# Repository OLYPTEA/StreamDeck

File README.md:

# KORE DECK

<h3 align="center">
Un Hub de Control Modulaire pour PC et Robotique/A Modular Stream Deck & Robotics Control Hub (cf : Robotic_Arm)
</h3>

---

##  Video de présentation/Cinematic Demo

https://github.com/user-attachments/assets/3f7520e6-ee07-4d92-a84f-97e8f2b0d568

---

## Description

Ce projet est un **Stream Deck DIY** développé dans le but d'être modulaire.  
Conçu autour d'un **ESP32-S3**, il permet de piloter des raccourcis PC, de monitorer des ressources, mais aussi de servir de **Hub de contrôle** pour des périphériques externes (bras robotique, capteurs) via un port d'extension dédié.

This project is a **DIY Stream Deck** designed to be modular.  
Built around an **ESP32-S3**, it allows you to control PC shortcuts, monitor system resources, and serve as a **control hub** for external devices (such as robotic arms and sensors) via a dedicated expansion port.

---

# Spécifications Matérielles

| Composant | Détails |
| :--- | :--- |
| **Microcontrôleur** | ESP32-S3 DevKit N16R8 (16MB Flash / 8MB PSRAM) |
| **Écran** | DWIN HMI 960x240 (Interface UART, protocole DGUS II) |
| **Capteurs** | 7x Switchs mécaniques (Cherry MX) + 4x Potentiomètres analogiques |
| **Alimentation** | USB-C natif (Compatible **Thunderbolt** pour forte puissance) |
| **Modularité** | Boîtier CAO avec pied indépendant et port d'extension I2C |

---

# Points Forts du Projet

## 1. Conception Modulaire (CAO)

Le boîtier a été conçu sous **Fusion 360** avec une approche modulaire :

- **Pied indépendant :**  
  Permet d'adapter différents angles ou supports (pince de bureau, bras articulé).

- **Port d'extension :**  
  Sortie des ports non-utilisés (SDA/SCL, 5V, GND) sur le côté pour connecter des modules sans ouvrir le boîtier.

- **Modularité du Software/Firmware**
  Pensé dans le but d'être mobile et évolutif (rajout facile à intégrer)

The Case was designed in **Fusion 360** using a modular approach:

- **Detachable stand:**  
  Allows for different angles or mounts (desk clamp, articulated arm).

- **Expansion port:**  
  Unused ports (SDA/SCL, 5V, GND) are routed to the side to connect modules without opening the enclosure.

- **Software/Firmware Modularity**
  Designed to be portable and scalable (easy to integrate new features)

---

## 2. Hub Robotique/Robotics Hub

Grâce au port d'extension, le Stream Deck peut piloter un **bras robotique** (servomoteurs) via un driver **PCA9685**.

- **Mapping dynamique :**  
  Les potentiomètres contrôlent directement les angles des servos lorsque le profil `Robot` est sélectionné.

- **Affichage temps réel :**  
  L'écran DWIN affiche l'état et la position de chaque articulation.

Thanks to the expansion port, the Stream Deck can control a **robotic arm** (servo motors) via a **PCA9685** driver.

- **Dynamic mapping:**  
  The potentiometers directly control the servo angles when the `Robot` profile is selected.

- **Real-time display:**  
  The DWIN screen displays the status and position of each joint.

---

## 3. Gestion de l'Énergie/Energy Management

Optimisation pour le **Thunderbolt** :

- Alimentation directe des périphériques (Écran, Servos) via la ligne **5V/Vin** pour préserver le régulateur interne de l'ESP32.

- Filtrage matériel par condensateurs (`470µF` → `1000µF`) pour stabiliser les pics de courant des moteurs.

Optimization for **Thunderbolt**:

- Direct power supply to peripherals (display, servos) via the **5V/Vin** line to preserve the ESP32’s internal voltage regulator.

- Hardware filtering using capacitors (`470µF` → `1000µF`) to stabilize motor current spikes.

---

# Schéma de Câblage (Résumé)/Wiring Diagram (Summary)

Le projet utilise des techniques de filtrage pour garantir la précision des lectures analogiques :

- **Potentiomètres :**  
  Condensateurs de `100nF` pour le lissage du signal.

- **Boutons :**  
  Condensateurs de `10nF` pour le debounce matériel.

- **Communication Écran :**  
  Liaison série directe (`3.3V TTL`) sur `Rx2/Tx2`.

The project uses filtering techniques to ensure the accuracy of analog readings:

- **Potentiometers:**  
  `100nF` capacitors for signal smoothing.

- **Buttons:**  
  `10nF` capacitors for hardware debouncing.

- **Display communication:**  
  Direct serial connection (`3.3V TTL`) on `Rx2/Tx2`.

---

# Structure du Dépôt/Structure of the Repository

```text
├── Hardware/           # Fichiers STEP/STL (Fusion 360)/STEP/STL files (Fusion 360)
├── Firmware/           # Code source ESP32 (Arduino IDE / PlatformIO)/ESP32 source code (Arduino IDE / PlatformIO)
├── DWIN_Project/       # Fichiers de configuration DGUS II (Interface graphique)/DGUS II Configuration Files (Graphical Interface)
├── Scripts_PC/         # Script de détection d'application (Python/C#)/Application detection script (Python/C#)
└── Assets/             # Icônes, vidéos et ressources graphiques/Icons, videos, and graphic resources
```

---

# Roadmap

- [ ] Interface UI avancée/Advanced UI (check)
- [ ] Gestion multi-profils/Multi-profile management (check)
- [ ] Intégration MQTT/MQTT integration
- [ ] Contrôle robotique avancé/Advanced robotics control
- [ ] Support Wi-Fi / Bluetooth/Wi-Fi / Bluetooth support
- [ ] Intégration Home Assistant/Home Assistant integration

---

# Technologies Utilisées/Technologies Used

- **ESP32-S3**
- **DGUS II / DWIN HMI**
- **Fusion 360**
- **Arduino / PlatformIO**
- **Python / C++**
- **I2C / UART**
- **KicKad**

---

# Auteur/Author

Projet conçu et développé par **OLYPTEA** (Sacha Gibert).

Project designed and developed by **OLYPTEA** (Sacha Gibert).

GitHub :  
https://github.com/OLYPTEA

---

Mention à Andrei Doncescu : https://homepages.laas.fr/adoncesc/SystemEmbed/Filtrage.pdf, 
          Random Nerds Tutorial : https://randomnerdtutorials.com/esp32-save-data-permanently-preferences/, 
          cppreference.com : https://en.cppreference.com/cpp/language/static_cast,
          Peng Zhihui : https://github.com/peng-zhihui/HoloCubic <3,
          STMicroelectronics — AN2834 : https://www.st.com/resource/en/application_note/cd00211314-how-to-optimize-the-adc-accuracy-in-the-stm32-mcus-stmicroelectronics.pdf,
          Claude code : Débogage,
          Espressif Systems : https://documentation.espressif.com/esp32-s3_datasheet_en.pdf,
          Tauri : http://github.com/tauri-apps/tauri/blob/dev/ARCHITECTURE.md,
                  https://github.com/tauri-apps/awesome-tauri

---

Merci d'avoir pris le temps de regarder le projet

Thank you for taking the time to look at the project

---

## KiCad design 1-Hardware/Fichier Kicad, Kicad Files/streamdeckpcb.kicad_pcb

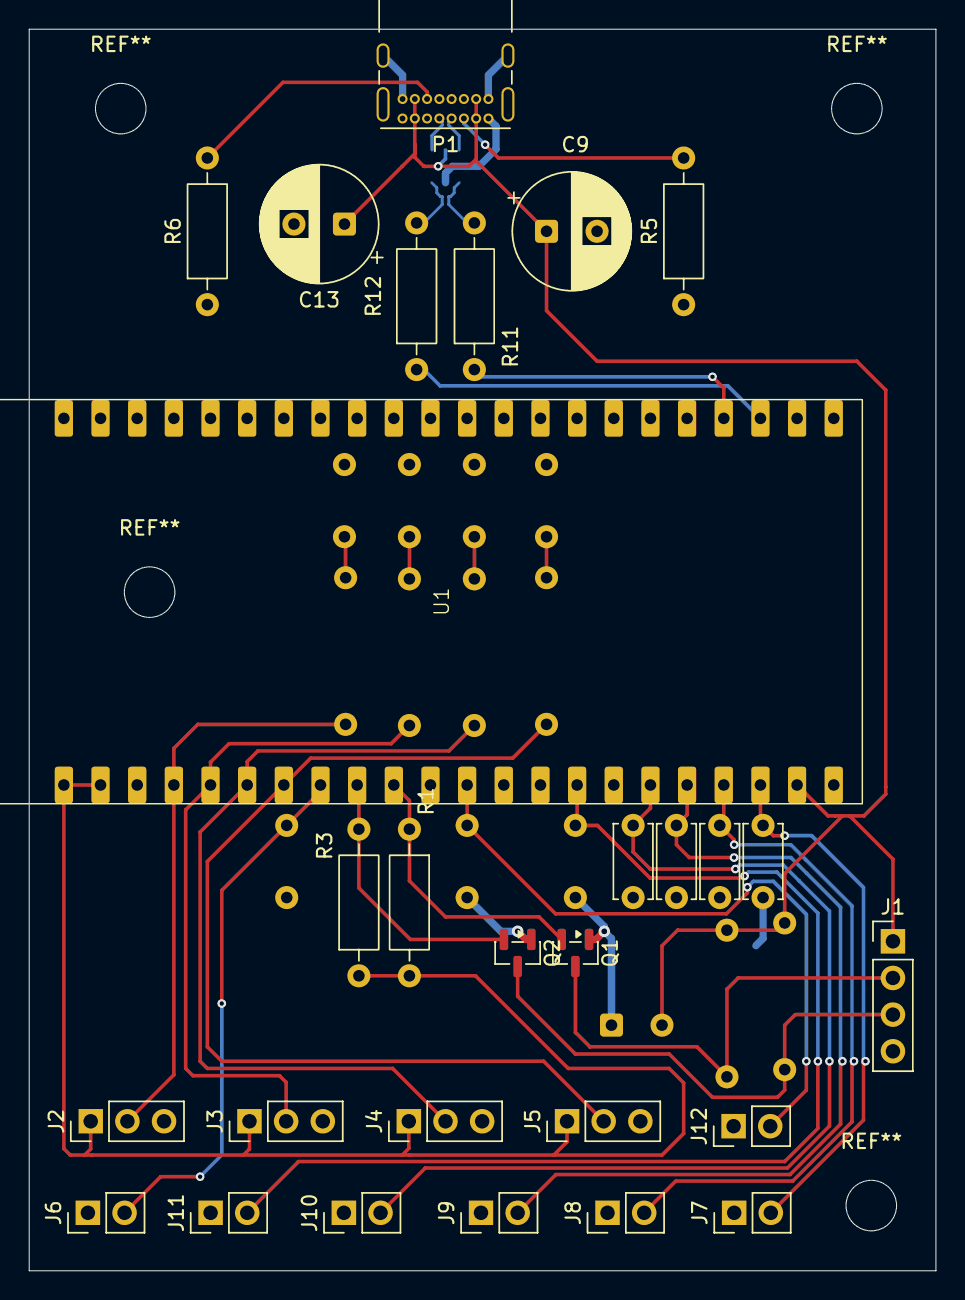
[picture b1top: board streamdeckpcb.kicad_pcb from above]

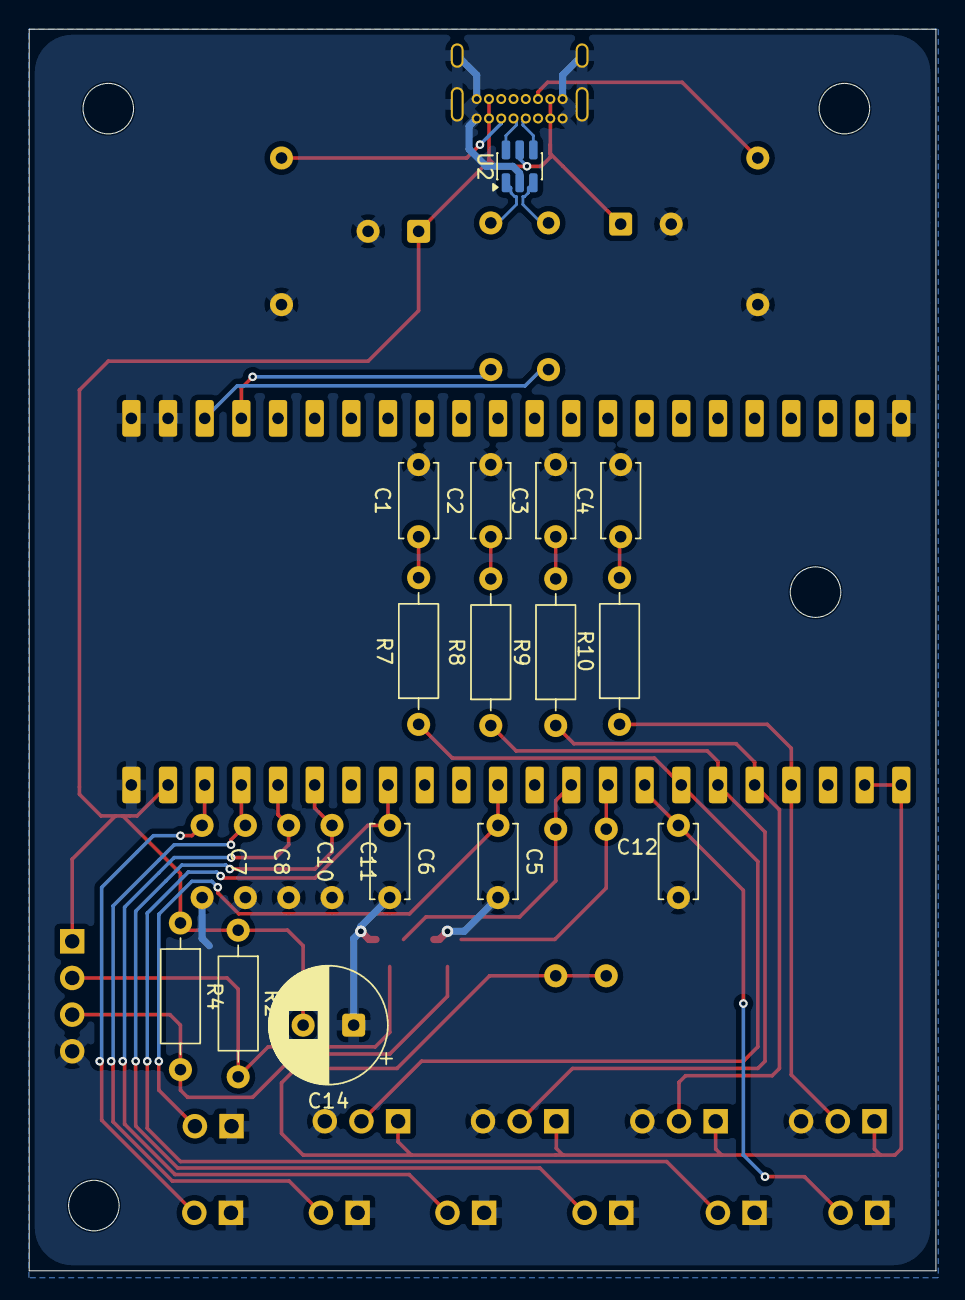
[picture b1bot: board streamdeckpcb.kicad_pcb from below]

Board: 2 copper layers, 62.8 x 86.0 mm, 43 parts (15 on the bottom side), 30 nets.

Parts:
C1, C2, C3, C4: 100nF; C_Disc_D5.0mm_W2.5mm_P5.00mm
C5, C6, C7, C8, C10, C11: 10nF; C_Disc_D5.0mm_W2.5mm_P5.00mm
C9, C14: 100nF; CP_Radial_D8.0mm_P3.50mm
C12: C; C_Disc_D5.0mm_W2.5mm_P5.00mm
C13: 10µF; CP_Radial_D8.0mm_P3.50mm
J1: dwin; PinHeader_1x04_P2.54mm_Vertical
J2: pot1; PinHeader_1x03_P2.54mm_Vertical
J3: pot2; PinHeader_1x03_P2.54mm_Vertical
J4: pot3; PinHeader_1x03_P2.54mm_Vertical
J5: pot4; PinHeader_1x03_P2.54mm_Vertical
J6, J11: but7; PinHeader_1x02_P2.54mm_Vertical
J7: but6; PinHeader_1x02_P2.54mm_Vertical
J8: but5; PinHeader_1x02_P2.54mm_Vertical
J9, J10: but3; PinHeader_1x02_P2.54mm_Vertical
J12: but1; PinHeader_1x02_P2.54mm_Vertical
P1: USB_C_Plug_USB2.0; USB_C_Receptacle_GCT_USB4085
Q1, Q2: BSS138; SOT-23
R1, R2, R3, R4: 10k; R_Axial_DIN0207_L6.3mm_D2.5mm_P10.16mm_Horizontal
R5, R6: 5.1K; R_Axial_DIN0207_L6.3mm_D2.5mm_P10.16mm_Horizontal
R7, R8, R9, R10: 1k; R_Axial_DIN0207_L6.3mm_D2.5mm_P10.16mm_Horizontal
R11, R12: 22Ω; R_Axial_DIN0207_L6.3mm_D2.5mm_P10.16mm_Horizontal
U1: Sans titre
U2: USBLC6-2SC6; SOT-23-6

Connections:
+3.3V: J2.1, J3.1, J4.1, J5.1, R1.2, R3.1, U1.3v3
+5V: C9.1, C13.1, C14.2, J1.1, P1.A4 (VBUS), P1.A9 (VBUS), P1.B4 (VBUS), P1.B9 (VBUS), R2.1, R4.1, U1.5vin, U2.5 (VBUS)
/Pot1Sign: J2.2, R10.1, U1.4
/Pot2Sign: J3.2, R9.1, U1.5
/Pot3Sign: J4.2, R8.1, U1.6
/Pot4Sign: J5.2, R7.1, U1.7
/RX0: Q2.2 (S), R3.2, U1.16
/TX0: Q1.2 (S), R1.1, U1.17
/USB+: P1.A6 (D+), U2.6 (I/O1)
/USB++: R11.1, U1.20
/USB-: P1.A7 (D-), U2.4 (I/O2)
/USB--: R12.1, U1.19
/but1sign: C5.1, J12.2, U1.8
/but2sign: C6.1, J11.2, U1.9
/but3sign: C7.1, J10.2, U1.11
/but4sign: C8.1, J9.2, U1.12
/but5sign: C10.1, J8.2, U1.13
/but6sign: C11.1, J7.2, U1.14
/but7sign: C12.1, J6.2, U1.15
/pin3Q1: J1.2, Q1.3 (D), R2.2
/pin3Q2: J1.3, Q2.3 (D), R4.2
/usb+: R11.2, U2.1 (I/O1)
/usb-: R12.2, U2.3 (I/O2)
GND: C1.2, C2.2, C3.2, C4.2, C5.2, C6.2, C7.2, C8.2, C9.2, C10.2, C11.2, C12.2, C13.2, C14.1, J1.4, J2.3, J3.3, J4.3, J5.3, J6.1, J7.1, J8.1, J9.1, J10.1, J11.1, J12.1, P1.A1 (GND), P1.A12 (GND), P1.B1 (GND), P1.B12 (GND), P1.SH (SHIELD), Q1.1 (G), Q2.1 (G), R5.1, R6.1, U1.GND, U2.2 (GND)
unnamed: C1.1, R7.2
unnamed: C2.1, R8.2
unnamed: C3.1, R9.2
unnamed: C4.1, R10.2
unnamed: P1.A5 (CC), R5.2
unnamed: P1.B5 (VCONN), R6.2

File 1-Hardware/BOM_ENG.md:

# BOM - ESP32-S3 Stream Deck / Control Panel

## Microcontroller
| Quantity | Component | Reference |
|---|---|---|
| 1 | ESP32-S3 DevKit | ESP32-S3 DevKit N16R8 |

---

## User Interface

### Potentiometers
| Quantity | Component | Value |
|---|---|---|
| 4 | Linear Potentiometer | B10K |

### Mechanical Switches
| Quantity | Component | Reference |
|---|---|---|
| 7 | Mechanical Keyboard Switch | Cherry MX |

### Display
| Quantity | Component | Reference |
|---|---|---|
| 1 | DWIN Display | DMG96240C037_03W |

---

## Transistors
| Quantity | Component | Reference |
|---|---|---|
| 2 | N-Channel MOSFET | BSS138 |

---

## Capacitors
| Quantity | Component | Value |
|---|---|---|
| 7 | Ceramic Capacitor | 10nF |
| 5 | Ceramic Capacitor | 100nF |
| 1 | Electrolytic Capacitor | 10µF |

---

## Resistors
| Quantity | Component | Value |
|---|---|---|
| 4 | Resistor | 10kΩ |
| 4 | Resistor | 1kΩ |
| 2 | Resistor | 5.1kΩ |

---

## Connectivity
| Quantity | Component | Reference |
|---|---|---|
| 1 | USB Type-C Connector | USB-C Port |

---

# Notes
- The 5.1kΩ resistors are used for USB-C CC1/CC2 configuration.
- The 100nF capacitors are used for power supply decoupling.
- The BSS138 MOSFETs are be used for logic level shifting (5V to 3.3V).
- The DWIN display generally communicates with the ESP32-S3 through UART.

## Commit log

2026-03-23 MajREADME
2026-05-11 Include cinematic demo video in README
    Add video demo to README
2026-05-11 Remove duplicate Cinematic Demo from README
    Removed duplicate Cinematic Demo section and its content.
2026-05-12 'MAJPROJET'
2026-05-15 Adding pcb, Gerbers Files...
2026-05-15 Update U1 part number in BOM_PCB.csv
    Updated the part number for U1 to specify 'ESP32 SPARKLE XH-S3E'.
2026-05-18 Fix typo in French thank you message
2026-05-18 Adding APP leak
2026-05-19 feat: Kore Deck v2.0 — App integration, Maj Software, Maj Firmware, Maj README
2026-05-19 Correct Python entry to C++ in README
2026-05-19 Revise README for IDE setup language update
    Updated README to include recommended IDE setup in French.
2026-05-19 Update roadmap with completed tasks
2026-05-19 Add KicKad to the tools list in README
2026-05-19 Format references in README.md
    Updated references to be comma-separated for better readability.
